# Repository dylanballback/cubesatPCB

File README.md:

# cubesatPCB
Cube-Sat PCB Files

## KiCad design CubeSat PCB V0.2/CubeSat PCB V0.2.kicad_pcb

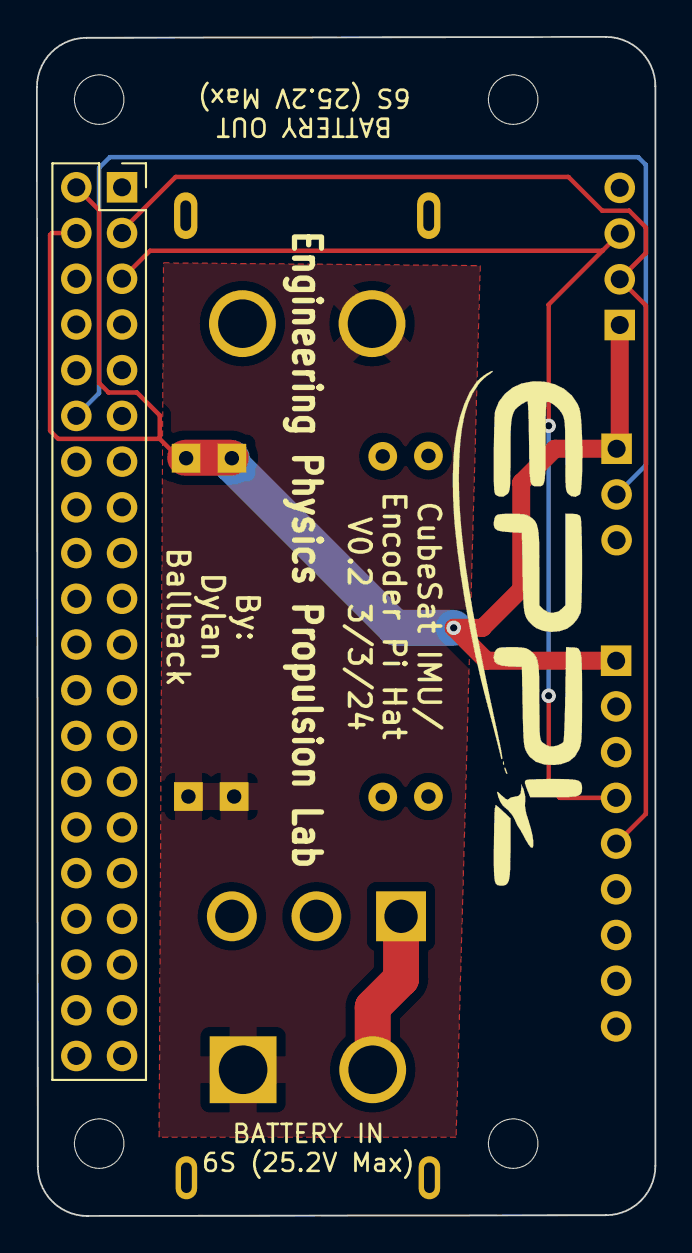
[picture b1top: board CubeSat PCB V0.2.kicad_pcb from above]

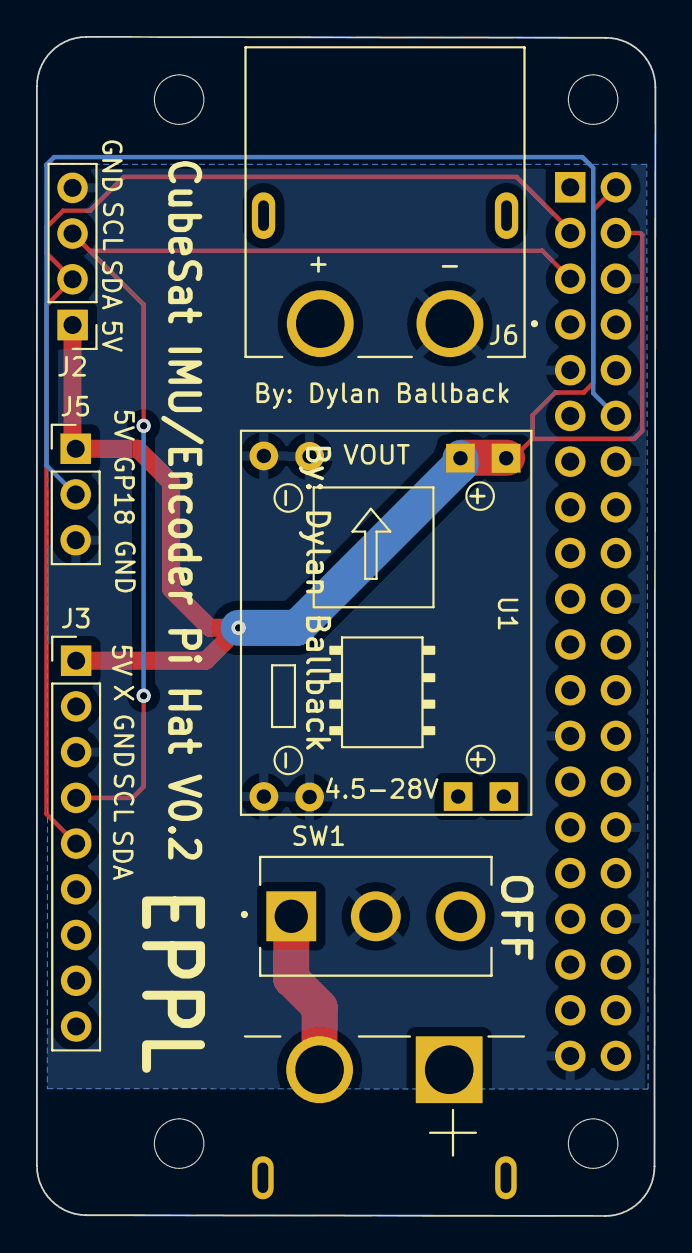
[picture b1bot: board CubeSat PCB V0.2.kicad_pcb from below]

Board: 2 copper layers, 34.4 x 65.5 mm, 8 parts (7 on the bottom side), 7 nets.

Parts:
J1: Raspberry_Pi_2_3; Raspberry_Pi_Zero_Socketed_THT_FaceDown_MountingHoles
J2: Encoder Connector; PinHeader_1x04_P2.54mm_Vertical
J3: LSM9DS1; PinHeader_1x09_P2.54mm_Vertical
J4: XT60PW-M; AMASS_XT60PW-M
J5: Conn_01x03_Female; PinHeader_1x03_P2.54mm_Vertical
J6: XT60PW-F; AMASS_XT60PW-F
SW1: SW_DPDT_x2; SW_500SSP1S2M2QEA
U1: MP1584EN; SRT_MPT1584EN_Module

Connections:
+5V: J1.2 (5V), J1.4 (5V), J2.1, J3.1, J5.1, U1.3 (Vout)
+BATT: J4.1 (+), J6.2 (+), U1.1 (Vin)
/SCL: J1.5 (SCL/GPIO3), J2.3, J3.4
/SDA: J1.3 (SDA/GPIO2), J2.2, J3.5
/led: J1.12 (GPIO18/PWM0), J5.2
GND: J1.6 (GND), J1.9 (GND), J1.14 (GND), J1.20 (GND), J1.25 (GND), J1.30 (GND), J1.34 (GND), J1.39 (GND), J2.4, J3.3, J5.3, J6.1 (-), SW1.2 (B), U1.2 (GND), U1.4 (GND)
unnamed: J4.2 (-), SW1.1 (A)

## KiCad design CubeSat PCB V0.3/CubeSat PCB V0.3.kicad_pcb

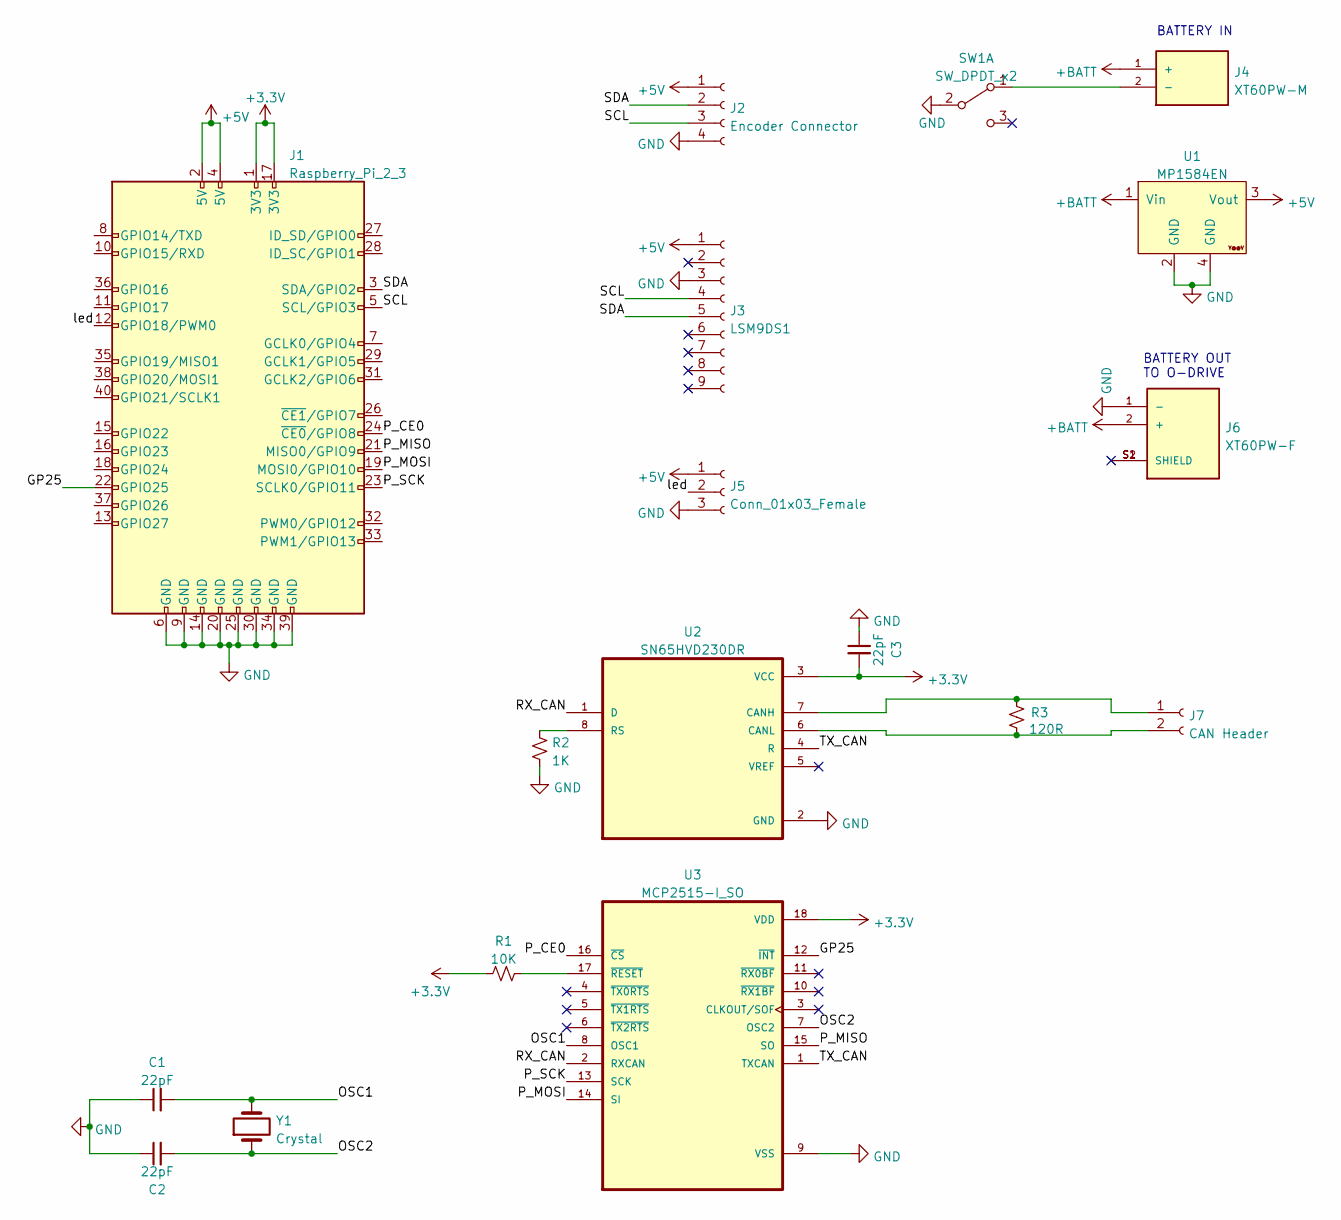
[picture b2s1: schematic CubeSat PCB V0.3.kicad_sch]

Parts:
C1, C2, C3: 22pF; C_1206_3216Metric_Pad1.33x1.80mm_HandSolder
J1: Raspberry_Pi_2_3; Raspberry_Pi_Zero_Socketed_THT_FaceDown_MountingHoles
J2: Encoder Connector; PinHeader_1x04_P2.54mm_Vertical
J3: LSM9DS1; PinHeader_1x09_P2.54mm_Vertical
J4: XT60PW-M; AMASS_XT60PW-M; PARTREV V1.2
J5: Conn_01x03_Female; PinHeader_1x03_P2.54mm_Vertical
J6: XT60PW-F; AMASS_XT60PW-F; PARTREV V1.2
J7: CAN Header; PinHeader_1x02_P2.54mm_Vertical
R1: 10K; R_0805_2012Metric_Pad1.20x1.40mm_HandSolder
R2: 1K; R_0805_2012Metric_Pad1.20x1.40mm_HandSolder
R3: 120R; R_0805_2012Metric_Pad1.20x1.40mm_HandSolder
SW1: SW_DPDT_x2; SW_500SSP1S2M2QEA
U1: MP1584EN; SRT_MPT1584EN_Module
U2: SN65HVD230DR; SOIC127P599X175-8N
U3: MCP2515-I_SO; SOIC127P1030X265-18N
Y1: Crystal; Crystal_SMD_HC49-US

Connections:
+3V3: C3.2, J1.1 (3V3), J1.17 (3V3), R1.1, U2.3 (VCC), U3.18 (VDD)
+5V: J1.2 (5V), J1.4 (5V), J2.1, J3.1, J5.1, U1.3 (Vout)
+BATT: J4.1 (+), J6.2 (+), U1.1 (Vin)
/GP25: J1.22 (GPIO25), U3.12 (~INT)
/OSC1: C1.2, U3.8 (OSC1), Y1.2
/OSC2: C2.2, U3.7 (OSC2), Y1.1
/P_CE0: J1.24 (~CE0/GPIO8), U3.16 (~CS)
/P_MISO: J1.21 (MISO0/GPIO9), U3.15 (SO)
/P_MOSI: J1.19 (MOSI0/GPIO10), U3.14 (SI)
/P_SCK: J1.23 (SCLK0/GPIO11), U3.13 (SCK)
/RX_CAN: U2.1 (D), U3.2 (RXCAN)
/SCL: J1.5 (SCL/GPIO3), J2.3, J3.4
/SDA: J1.3 (SDA/GPIO2), J2.2, J3.5
/TX_CAN: U2.4 (R), U3.1 (TXCAN)
/led: J1.12 (GPIO18/PWM0), J5.2
GND: C1.1, C2.1, C3.1, J1.6 (GND), J1.9 (GND), J1.14 (GND), J1.20 (GND), J1.25 (GND), J1.30 (GND), J1.34 (GND), J1.39 (GND), J2.4, J3.3, J5.3, J6.1 (-), R2.1, SW1.2 (B), U1.2 (GND), U1.4 (GND), U2.2 (GND), U3.9 (VSS)
unnamed: J4.2 (-), SW1.1 (A)
unnamed: J6.S1 (SHIELD), J6.S2 (SHIELD)
unnamed: J7.1, R3.2, U2.7 (CANH)
unnamed: J7.2, R3.1, U2.6 (CANL)
unnamed: R1.2, U3.17 (~RESET)
unnamed: R2.2, U2.8 (RS)

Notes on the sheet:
BATTERY IN
BATTERY OUT TO O-DRIVE

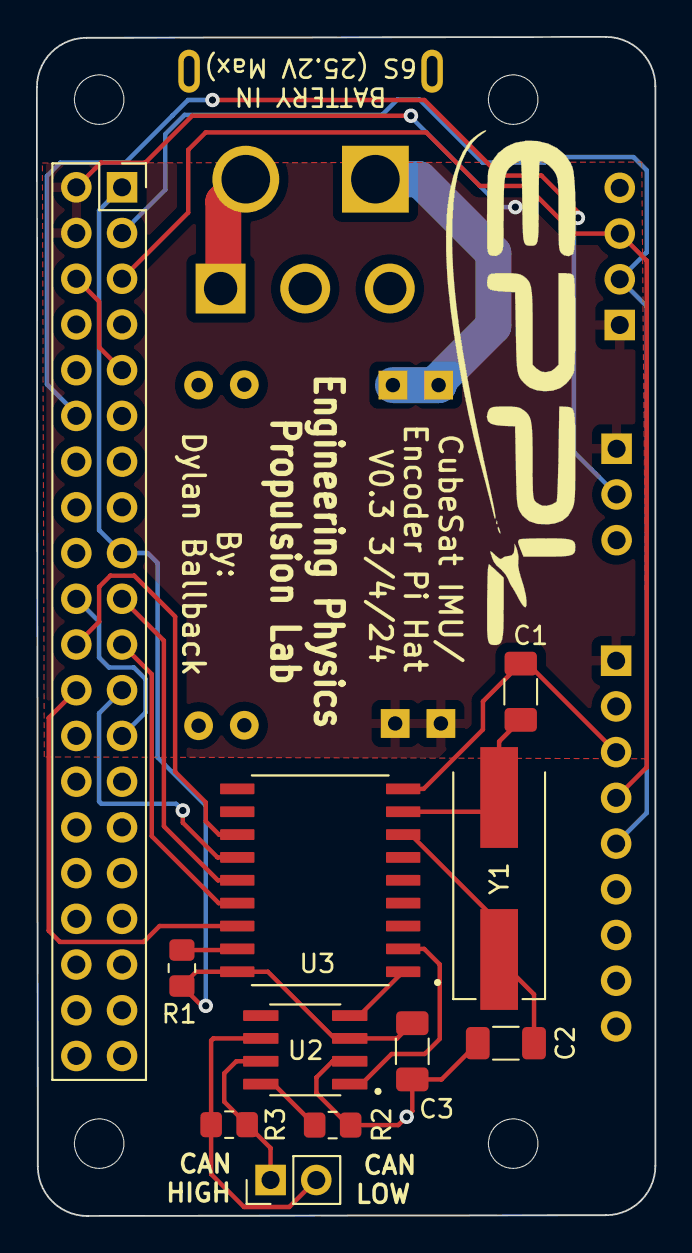
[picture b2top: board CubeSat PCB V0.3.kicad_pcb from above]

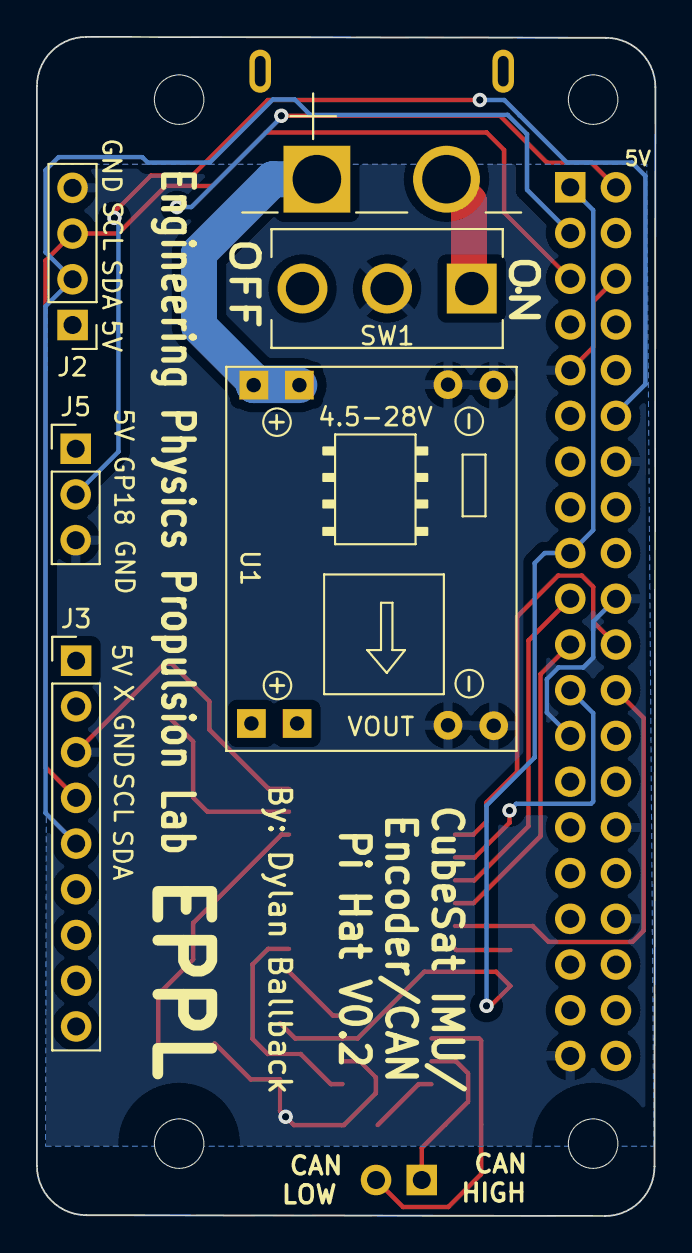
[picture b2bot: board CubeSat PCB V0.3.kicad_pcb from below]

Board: 2 copper layers, 34.4 x 65.5 mm, 17 parts (6 on the bottom side), 21 nets.

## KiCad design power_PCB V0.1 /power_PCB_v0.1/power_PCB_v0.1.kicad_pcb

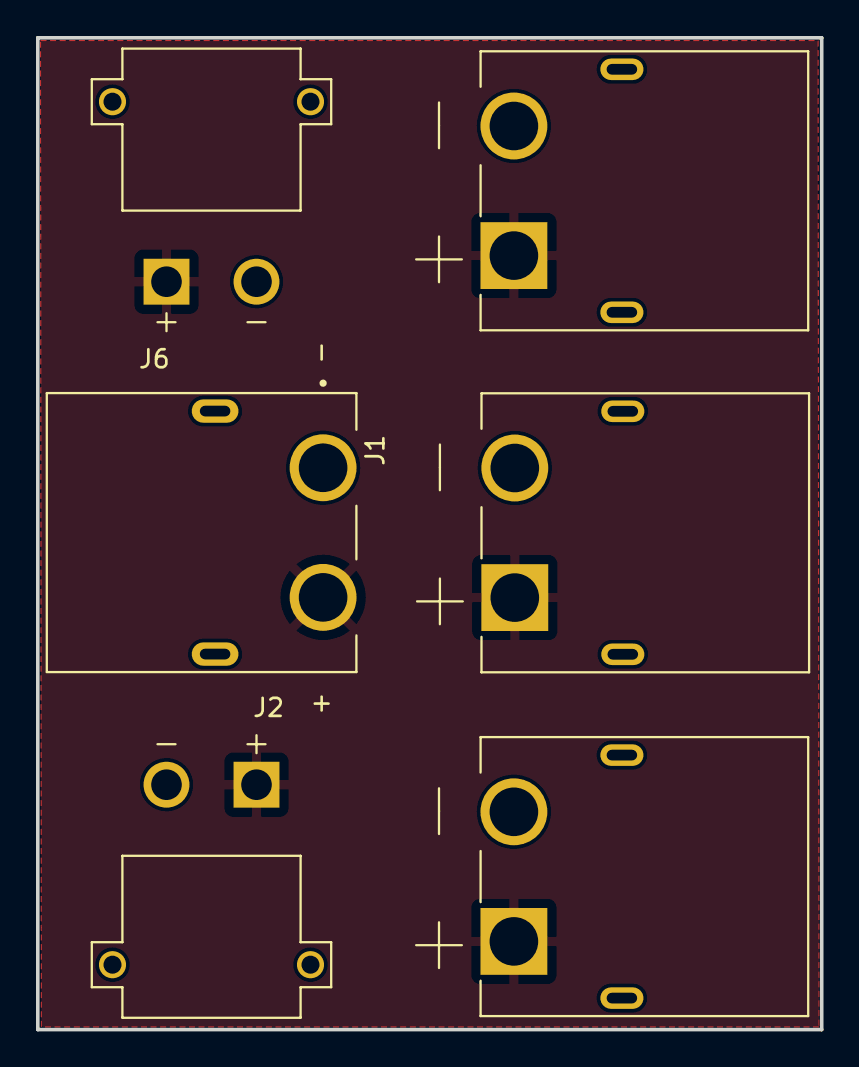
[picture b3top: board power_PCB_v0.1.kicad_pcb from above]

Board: 2 copper layers, 43.5 x 55.1 mm, 6 parts (0 on the bottom side), 2 nets, no tracks yet.

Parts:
J1: XT60PW-F; AMASS_XT60PW-F
J2, J6: XT30PW-M; AMASS_XT30PW-M
J3, J4, J5: XT60PW-M; AMASS_XT60PW-M

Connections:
+BATT: J1.2 (+), J2.P, J3.1 (+), J4.1 (+), J5.1 (+), J6.P
-BATT: J1.1 (-), J2.N, J3.2 (-), J4.2 (-), J5.2 (-), J6.N
